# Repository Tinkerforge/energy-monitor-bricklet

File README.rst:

Energy Monitor Bricklet
=======================

This repository contains the firmware source code and the hardware design
files. The documentation generator configs can be found at
https://github.com/Tinkerforge/generators

Repository Content
------------------

software/:
 * examples/: Examples for all supported languages
 * build/: Compiled files
 * src/: Source code of firmware
 * Makefile: Makefile to build project

hardware/:
 * Contains KiCad project files and additionally schematics as PDF

datasheets/:
 * Contains datasheets for sensors and complex ICs that are used

Hardware
--------

The hardware is designed with the open source EDA Suite KiCad
(http://www.kicad.org). Before you are able to open the files,
you have to install the Tinkerforge kicad-libraries
(https://github.com/Tinkerforge/kicad-libraries). You can either clone
them directly in hardware/ or clone them in a separate folder and
symlink them into hardware/
(ln -s kicad_path/kicad-libraries project_path/hardware). After that you
can open the .pro file in hardware/ with KiCad and from there view and
modify the schematics and the PCB layout.

Software
--------

If you want to do your own Brick/Bricklet firmware development we highly
recommend that you use our build environment setup script and read the
tutorial (https://www.tinkerforge.com/en/doc/Tutorials/Tutorial_Build_Environment/Tutorial.html).

To compile the C code we recommend you to install the newest GNU Arm Embedded
Toolchain (https://launchpad.net/gcc-arm-embedded/+download).
You also need to install bricklib2 (https://github.com/Tinkerforge/bricklib2).

You can either clone it directly in software/src/ or clone it in a
separate folder and symlink it into software/src/
(ln -s bricklib_path/bricklib2 project_path/software/src/). Finally make sure to
have CMake installed (http://www.cmake.org/cmake/resources/software.html).

After that you can build the firmware by invoking make in software/.
The firmware (.zbin) can then be found in software/build/ and uploaded
with brickv (click button "Flashing" on start screen).

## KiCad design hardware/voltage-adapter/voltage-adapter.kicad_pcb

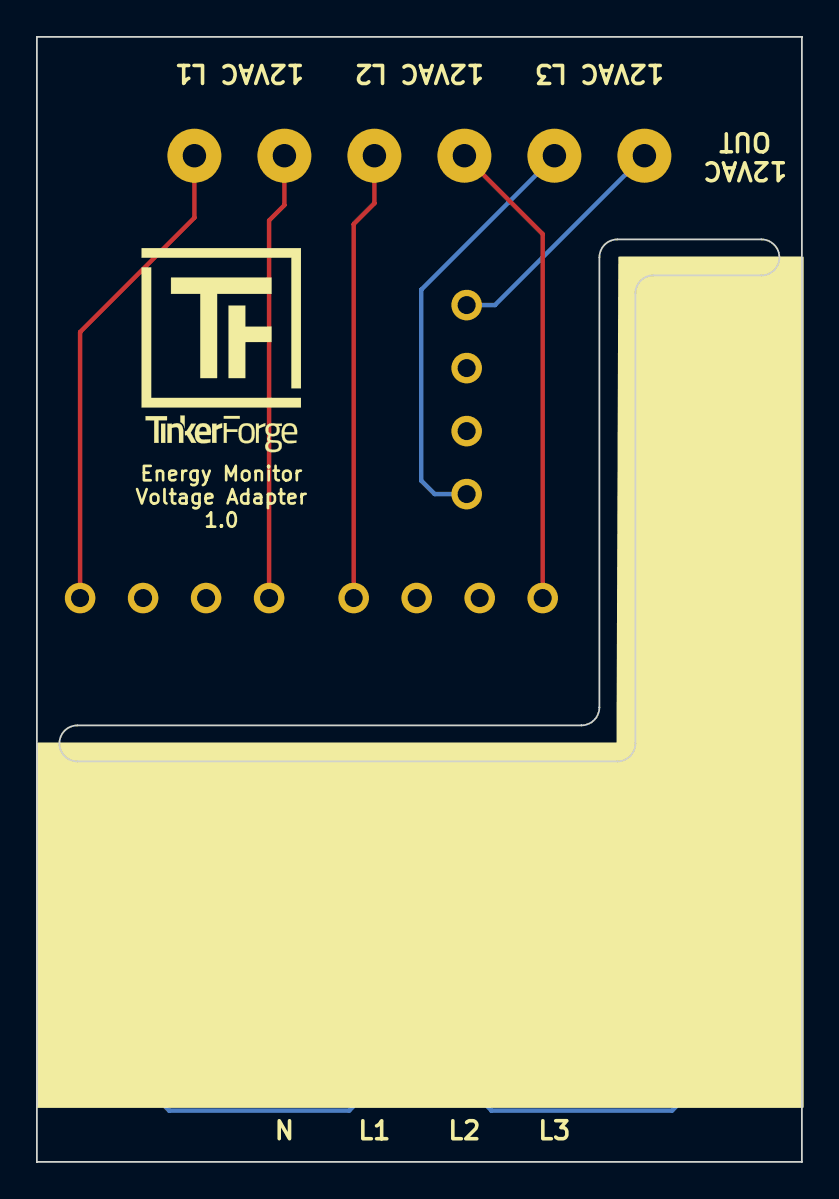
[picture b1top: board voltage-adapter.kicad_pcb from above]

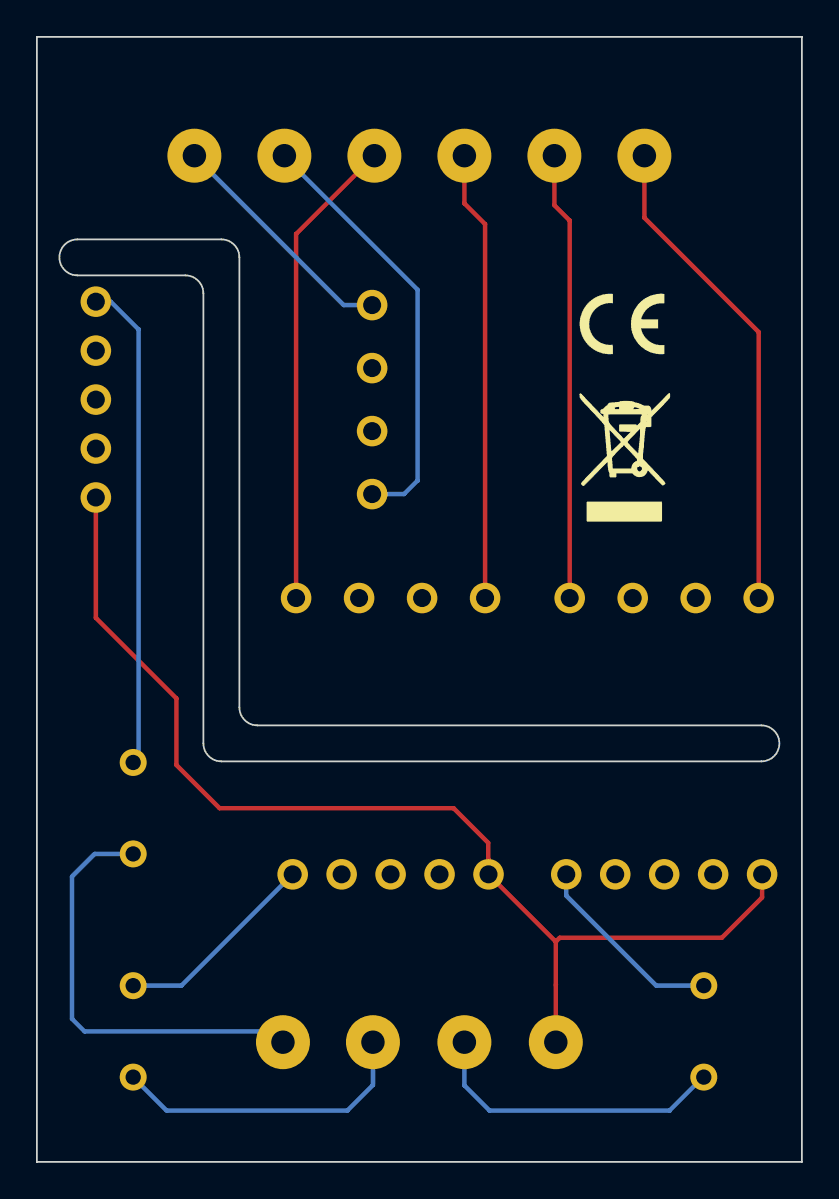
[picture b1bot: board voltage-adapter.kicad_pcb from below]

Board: 2 copper layers, 42.5 x 62.5 mm, 11 parts (2 on the bottom side), 13 nets.

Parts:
F1, F2, F3: MRF 50mA T; Fuse-MRF
P1: CONN_01X04; AKL_5_4
P3, P4: CONN_01X06; AKL_5_3
U1, U2, U3: Trafo-749118115; 749118115
VAL: WEEE_7mm
VAL#2: CE_5mm

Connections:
unnamed: F1.1, P1.2
unnamed: F1.2, U1.5
unnamed: F2.1, P1.3
unnamed: F2.2, U2.5
unnamed: F3.1, P1.4
unnamed: F3.2, U3.5
unnamed: P1.1, U1.1, U2.1, U3.1
unnamed: P3.1, U1.9
unnamed: P3.2, U1.6
unnamed: P3.3, U2.9
unnamed: P4.1, U2.6
unnamed: P4.2, U3.9
unnamed: P4.3, U3.6

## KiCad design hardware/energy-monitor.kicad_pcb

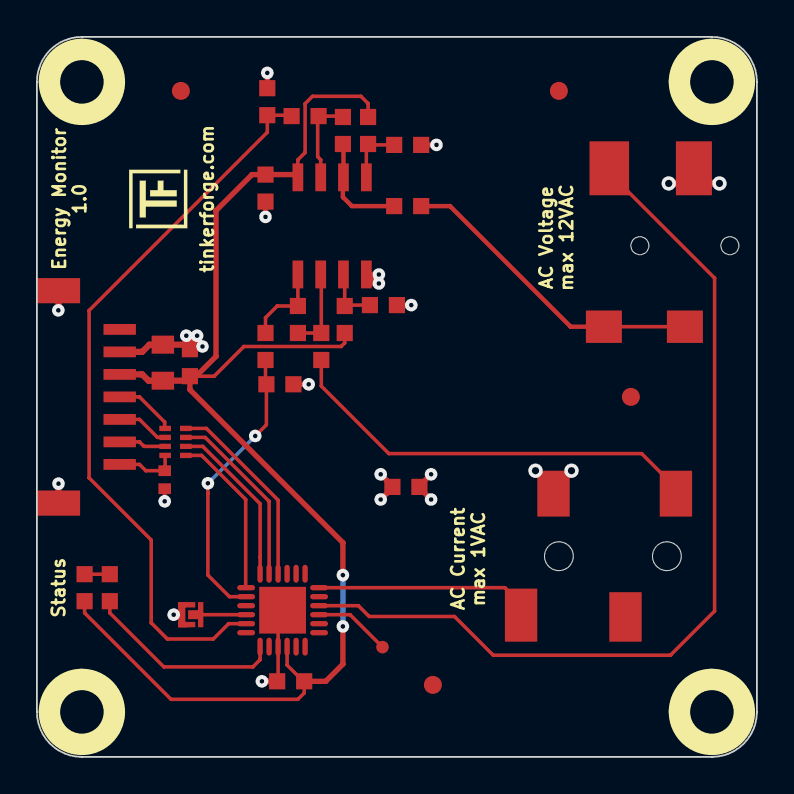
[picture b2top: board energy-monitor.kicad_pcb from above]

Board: 2 copper layers, 40.0 x 40.0 mm, 38 parts (2 on the bottom side), 27 nets.

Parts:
C1: 10uF; C0805
C2, C7: 100nF; C0603F
C3, C4: 180pF; C0603F
C5: 220pF; C0402F
C6: 1uF; C0603F
D3: blue; D0603F
Fiducial_Mark: VAL**; Fiducial_Mark
Fiducial_Mark#2, Fiducial_Mark#3, Fiducial_Mark#4: VAL**; Fiducial_Mark
P1: CON-SENSOR2
P3: BOOT; SolderJumper
P4: DEBUG; DEBUG_PAD
R1: 68.1; R0603F
R2: 0; R0603F
R3: 91k; R0603F
R4, R10: 9,1k; R0603F
R5: 68k; R0603F
R6: 33k; R0603F
R7: 68,1; R0603F
R8: 1k; R0603F
R9: 5,6k; R0603F
R11: 75k; R0603F
R12: 11k; R0603F
RP1: 82; 4X0402
U1: XMC1300; QFN24-4x4mm-0.5mm
U2: TLV272IS; SOIC8
U3, U4, U5, U6: DRILL; DRILL_NP
U7: phone-jack; PJ-327C-3
U8: barrel-plug; DC-033
VAL: WEEE_7mm
VAL#2: CE_5mm

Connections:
3V3: C1.1, C2.2, C6.1, C7.2, D3.1, P1.3, R6.2, R12.1, U1.10, U2.8
AGND: C2.1, C3.1, C4.2, R2.2, R4.2, R10.2, U2.4, U7.3, U8.2
AnalogA: C3.2, R1.1, U1.2
AnalogV: C4.1, R7.2, U1.5
GND: C1.2, C5.2, C6.2, C7.1, P1.2, P1.EP, P3.1, R2.1, U1.9, U1.EXP
unnamed: C5.1, P1.7, RP1.4
unnamed: D3.2, R8.2
unnamed: P1.4, RP1.1
unnamed: P1.5, RP1.2
unnamed: P1.6, RP1.3
unnamed: P3.2, U1.4
unnamed: P4.1, U1.15
unnamed: R1.2, R3.1, U2.1
unnamed: R3.2, R5.1, U2.2
unnamed: R4.1, R6.1, U2.3
unnamed: R5.2, U7.1
unnamed: R7.1, R9.2, U2.7
unnamed: R8.1, U1.7
unnamed: R10.1, R12.2, U2.5
unnamed: R11.1, U8.1
unnamed: R9.1, R11.2, U2.6
PlugA: U1.18, U7.4
PlugV: U1.16, U8.3
S-CLK: RP1.7, U1.23
S-CS: RP1.8, U1.22
S-MISO: RP1.5, U1.1
S-MOSI: RP1.6, U1.24

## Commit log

2019-02-12 New repository. Added readme, gitignore, datasheet, schematic
2019-02-12 added pcb design
2019-02-12 fix sym lib table, change pcb texts
2019-02-12 changed text layout, added fiducialmarks, ready for prototype
2019-03-07 changed resistor value for voltage measurement
2019-03-07 changed resistor values
2019-03-20 Add auto-generated firmware stub
2019-03-28 Add implementation of main API
2019-03-28 Add transformer calibration and status support
2019-03-28 Remove GPIO debug
2019-03-28 Add Energy Data Callback support
2019-03-28 Use tabs instead of spaces
2019-03-28 Make sure that there can never be a division by zero
2019-03-28 Use exact units in comment
2019-04-29 changed resistor values, bigger footprint for dc-033, changed labeling
2019-04-29 Fix V ADC pin
2019-04-29 changed AnalogV pin from 2.2 to 2.7/2.8
2019-04-30 Update voltage/current ratio (values from actual transformer)
2019-05-03 Add auto-generated examples
2019-05-09 fix footprint
2019-06-13 fix connector properties
2019-08-14 Turn logging off
2019-08-14 Add changelog entry for inital version
2019-08-15 add 3d data
2019-08-15 add schematic
2019-08-16 changed processor to XMC1300
2019-08-22 c: Adapt to bindings changes
2019-08-22 rust: Style cleanup
2019-08-22 Remove develpment marker
2019-08-23 Examples: Fix spelling of frequency.
2019-09-09 Remove unused debug output
2019-09-09 Fix typo
2019-09-09 Show voltage and current of 0 if the waveform has no zero-crossings
2019-09-09 Add ref for 2.0.1
2020-01-13 examples: Use python3 input instead of python2 raw_input.
2020-01-13 examples: mqtt: Remove trailing whitespace.
2020-07-17 examples: Fix typo
2020-08-05 added voltage adapter
2020-08-19 Add uc examples.
2020-08-25 uc: Fix whitespace
2020-08-27 uc: Fix warnings.
2020-09-02 uc: Add example driver note.
2020-10-16 uc: Fix divisor type.
2020-10-26 examples: Fix typos in comments
2021-10-25 Update KiCad link
    https://www.kicad.org/blog/2021/10/Avoid-links-to-former-kicad-domain/
2022-04-19 examples: uc: Rename TF_HalContext to TF_HAL.
2022-04-27 uc: Adapt to bindings changes
2022-07-06 Add license files.
2025-10-04 Fix compatibility with new Docker build image (GCC 14.2.1)

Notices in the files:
hardware/energy-monitor.kicad_pcb:
Licensed under CERN OHL v.1.1
Copyright (©) 2019, T.Schneidermann
hardware/voltage-adapter/voltage-adapter.kicad_pcb:
Copyright (©) 2020, T.Schneidermann
Copyright Tinkerforge GmbH 2020.
This documentation describes Open Hardware and is licensed under the
CERN OHL v. 1.1.
